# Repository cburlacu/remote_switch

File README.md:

# About

If you need to press the power button of your laptop remotely you may use this :)

# Prerequisites
* Kicad:   https://kicad-pcb.org/download
* ESP SDK: https://github.com/pfalcon/esp-open-sdk.git
* uPython: https://github.com/micropython/micropython.git

# Hardware
```
https://esp8266.ru/wp-content/uploads/scheme-full-autoprog1-1024x586.jpg
https://github.com/esp8266/esp8266-wiki/wiki/Boot-Process
```
# TODO
- 10k resistor to ground for GPIO15/MTDO

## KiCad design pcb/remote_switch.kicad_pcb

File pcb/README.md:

Using the footprint of ESP8266 from https://github.com/jdunmire/kicad-ESP8266.git

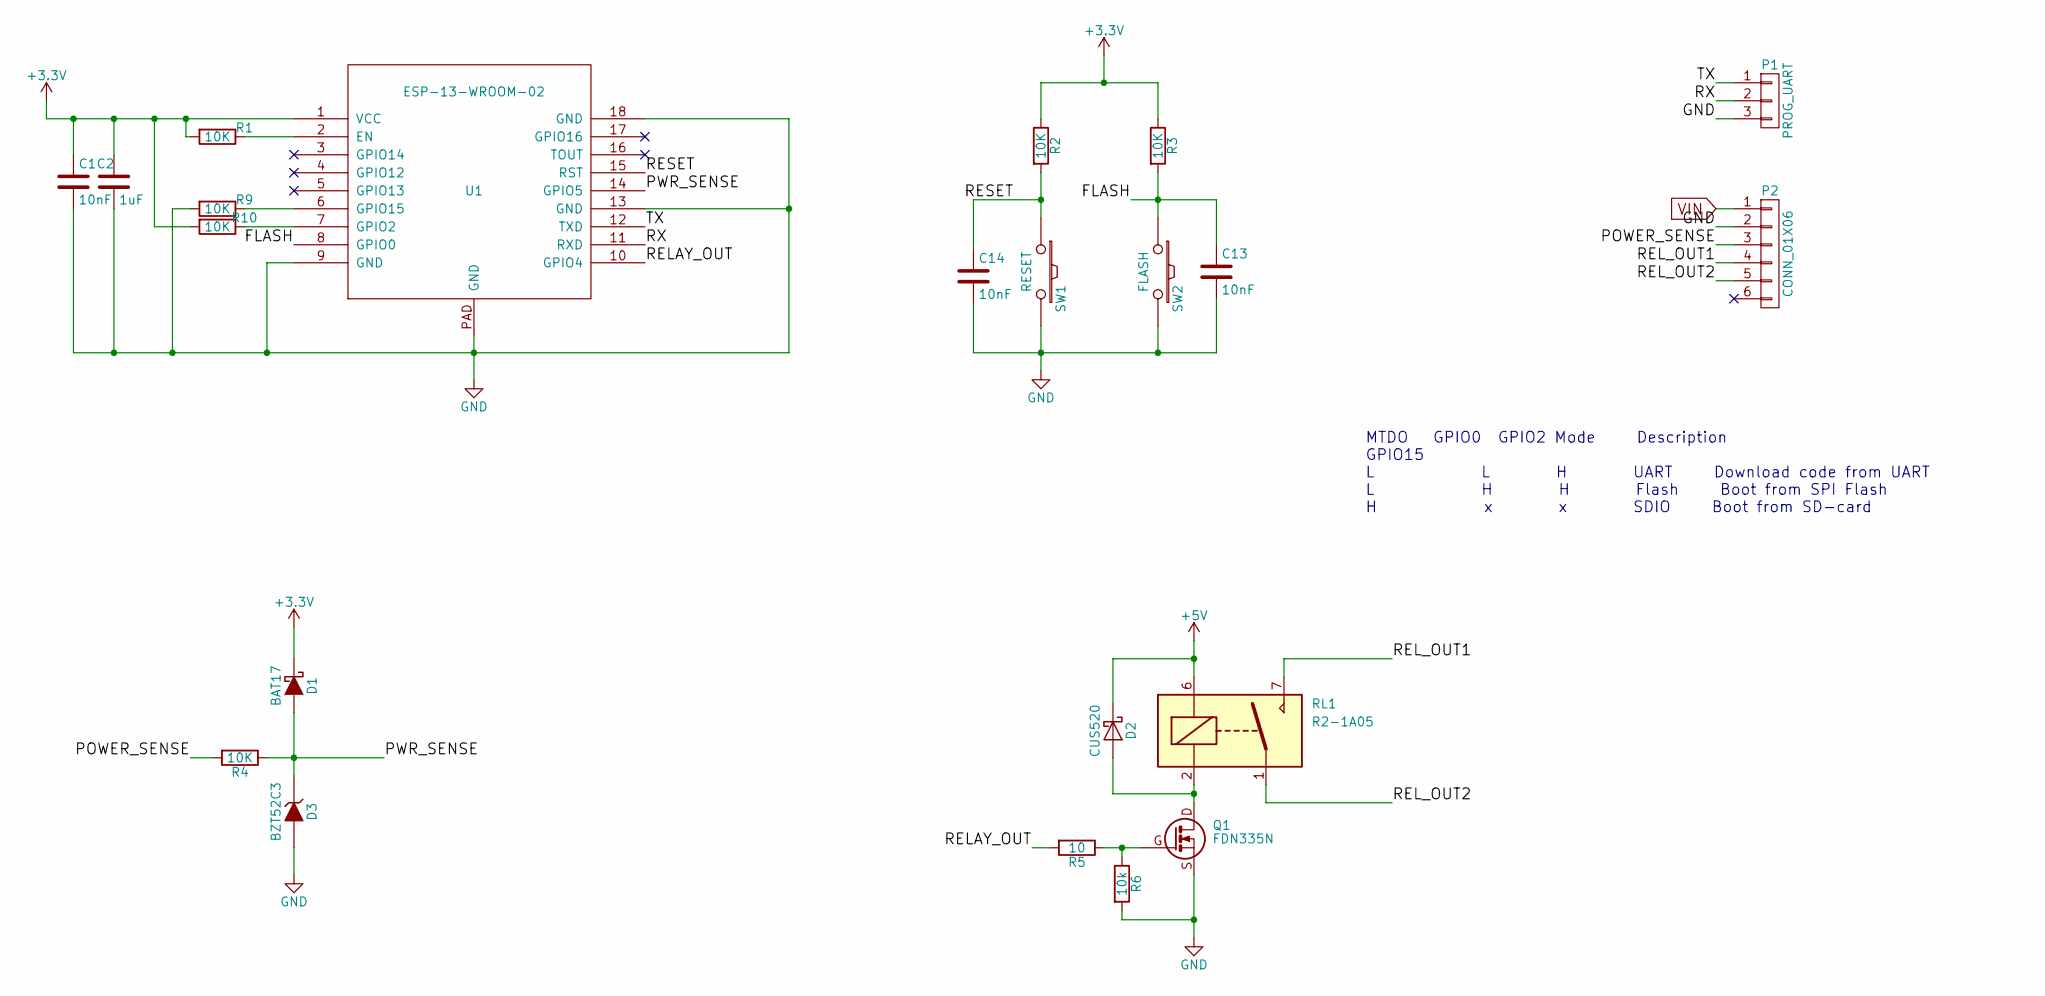
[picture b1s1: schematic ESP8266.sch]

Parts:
C1, C13, C14: 10nF; C_1206_HandSoldering
C2: 1uF; C_1206_HandSoldering
D1: BAT17; SOT-23
D2: CUS520; SOD-323_HandSoldering
D3: BZT52C3; SOD-123
P1: PROG_UART; PINHEAD1-3
P2: CONN_01X06; CON6_1X6_RHK_MINICT
Q1: FDN335N
R1, R2, R3, R4, R9, R10: 10K; R_1206_HandSoldering
R5: 10; R_1206_HandSoldering
R6: 10k; R_1206_HandSoldering
RL1: R2-1A05; R2-1A05_2
SW1: RESET; SW_SPST_B3S-1000
SW2: FLASH; SW_SPST_B3S-1000
U1: ESP-13-WROOM-02

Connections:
+3V3: C1.1, C2.1, D1.3 (K), R1.2, R2.1, R3.1, R10.2, U1.1 (VCC); also elsewhere on the board
+5V: D2.1 (K), RL1.6; also elsewhere on the board
/ESP8266/FLASH: C13.1, R3.2, SW2.1, U1.8 (GPIO0)
/ESP8266/POWER_SENSE: P2.3, R4.2
/ESP8266/PWR_SENSE: D1.1 (A), D3.1 (K), R4.1, U1.14 (GPIO5)
/ESP8266/RELAY_OUT: R5.2, U1.10 (GPIO4)
/ESP8266/REL_OUT1: P2.4, RL1.7
/ESP8266/REL_OUT2: P2.5, RL1.1
/ESP8266/RESET: C14.1, R2.2, SW1.1, U1.15 (RST)
/ESP8266/RX: P1.2, U1.11 (RXD)
/ESP8266/TX: P1.1, U1.12 (TXD)
GND: C1.2, C2.2, C13.2, C14.2, D3.2 (A), P1.3, P2.2, Q1.S, R6.2, R9.2, SW1.2, SW2.2, U1.9 (GND), U1.13 (GND), U1.18 (GND), U1.PAD (GND); also elsewhere on the board
unnamed: D2.2 (A), Q1.D, RL1.2
unnamed: Q1.G, R5.1, R6.1
unnamed: R1.1, U1.2 (EN)
unnamed: R9.1, U1.6 (GPIO15)
unnamed: R10.1, U1.7 (GPIO2)
VIN: P2.1; also elsewhere on the board

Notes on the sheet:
MTDO GPIO0 GPIO2 Mode Description GPIO15 L L H UART Download code from UART L H H Flash Boot from SPI Flash H x x SDIO Boot from SD-card

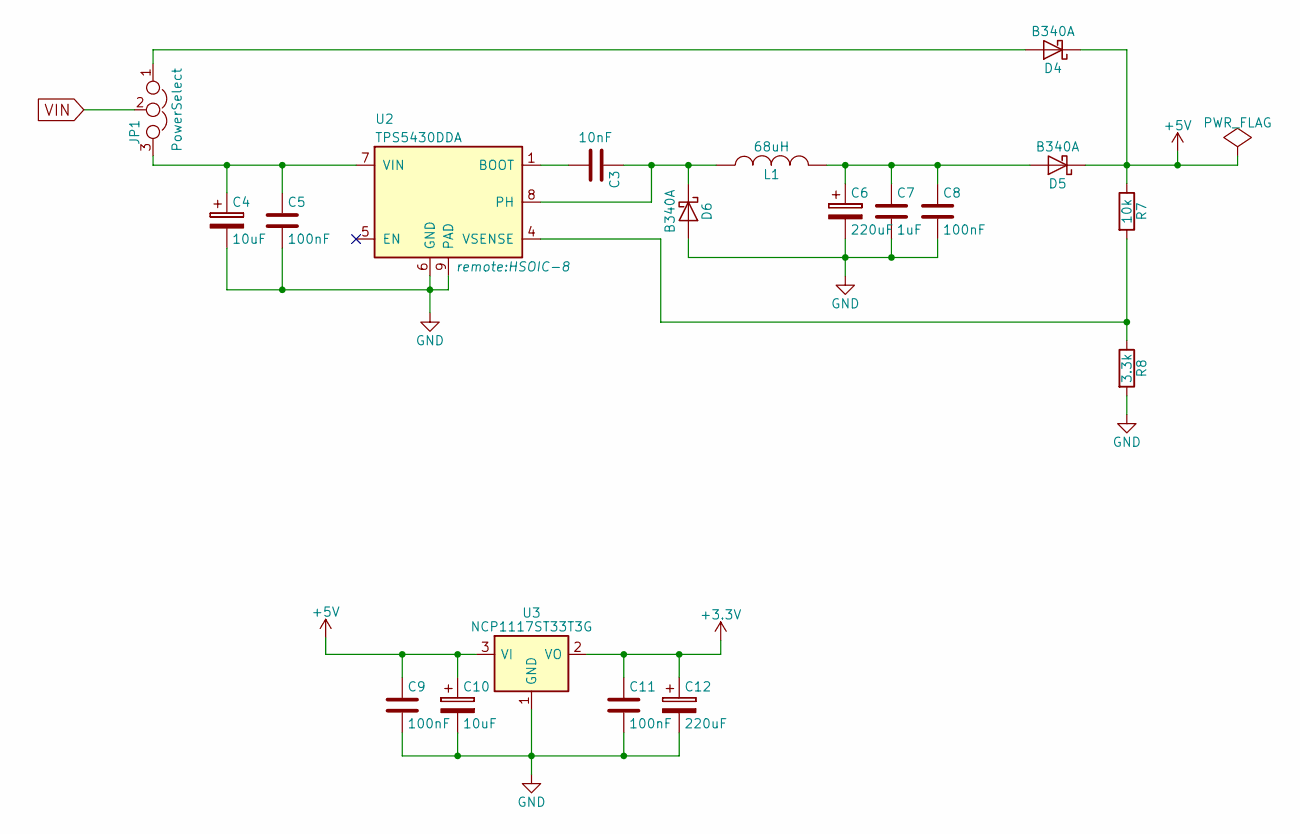
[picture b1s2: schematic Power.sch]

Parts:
C3: 10nF; C_1206_HandSoldering
C4, C10: 10uF; c_elec_5x5.8
C5, C8, C9, C11: 100nF; C_1206_HandSoldering
C6, C12: 220uF; c_elec_6.3x7.7
C7: 1uF; C_1206_HandSoldering
D4, D5, D6: B340A; SMA_Handsoldering
JP1: PowerSelect; PINHEAD1-3
L1: 68uH; DL50
R7: 10k; R_1206_HandSoldering
R8: 3.3k; R_1206_HandSoldering
U2: TPS5430DDA; HSOIC-8
U3: NCP1117ST33T3G; NCP1117-SOT32

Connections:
+3V3: C11.1, C12.1, U3.2 (VO); also elsewhere on the board
+5V: C9.1, C10.1, D4.1 (K), D5.1 (K), R7.1, U3.3 (VI); also elsewhere on the board
GND: C4.2, C5.2, C6.2, C7.2, C8.2, C9.2, C10.2, C11.2, C12.2, D6.2 (A), R8.2, U2.6 (GND), U2.9 (PAD), U3.1 (GND); also elsewhere on the board
unnamed: C3.1, D6.1 (K), L1.1, U2.8 (PH)
unnamed: C3.2, U2.1 (BOOT)
unnamed: C4.1, C5.1, JP1.3, U2.7 (VIN)
unnamed: C6.1, C7.1, C8.1, D5.2 (A), L1.2
unnamed: D4.2 (A), JP1.1
unnamed: R7.2, R8.1, U2.4 (VSENSE)
VIN: JP1.2; also elsewhere on the board

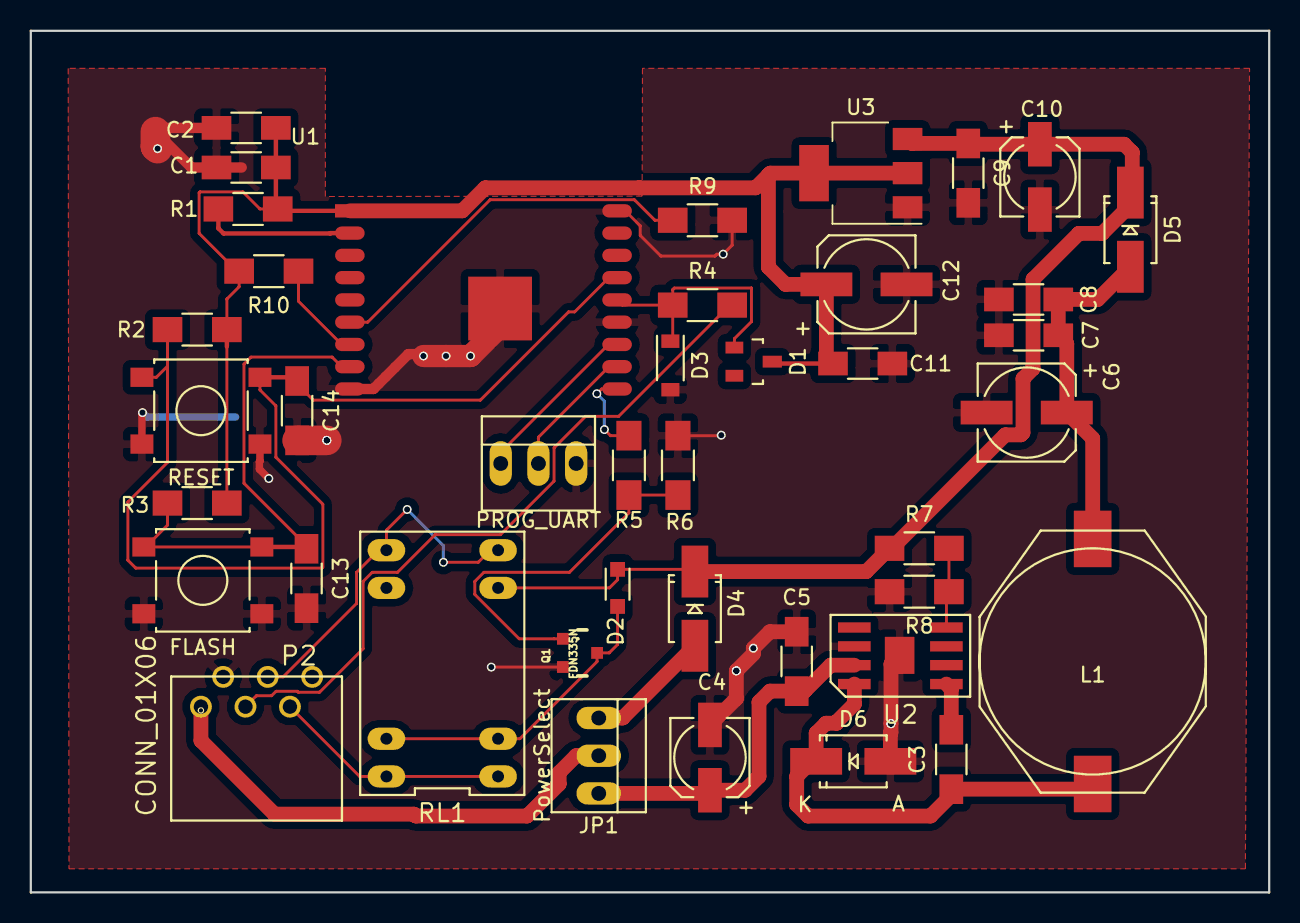
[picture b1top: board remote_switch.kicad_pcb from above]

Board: 2 copper layers, 83.4 x 58.0 mm, 41 parts (0 on the bottom side), 24 nets.

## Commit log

2017-01-20 Update README.md file
2017-01-20 Update the readme
2017-12-29 Update TODO
